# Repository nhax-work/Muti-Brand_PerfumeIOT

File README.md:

# Chạy dự án ở máy local — Hướng dẫn cho người mới

Tài liệu này giải thích **cách dựng database (và các dịch vụ đi kèm) trên máy của bạn** bằng Docker Compose, theo cách dễ hiểu nhất có thể. Đọc xong là chạy được, không cần biết Docker trước.

---

## 1. Docker Compose là gì, hiểu đơn giản

Coi `docker-compose.yml` như một **công thức nấu ăn**: nó ghi "cần 1 nồi Postgres, 1 nồi Redis, 1 nồi MQTT...". Khi bạn gõ lệnh `docker compose up`, máy bạn sẽ tự tải và bật các "nồi" đó lên — **trên chính máy bạn**, không đụng vào máy ai khác.

Điều quan trọng cần nhớ:

> **Database bằng Docker Compose là của riêng từng người.** Máy bạn có một DB, máy đồng đội có một DB khác. Hai DB này *không tự động giống nhau* — ban đầu cả hai đều **trống trơn**, không có bảng nào cả.

Vậy làm sao để DB của mọi người giống nhau? Câu trả lời ở mục 4.

---

## 2. Chuẩn bị lần đầu (chỉ làm 1 lần)

**Bước 1 — Cài Docker Desktop** (nếu chưa có): tải tại docker.com, cài xong nhớ mở app Docker Desktop lên và để nó chạy nền.

**Bước 2 — Tạo file cấu hình riêng của bạn:**

```bash
cp .env.example .env
```

File `.env` chứa các thông tin như tên user DB, mật khẩu, cổng kết nối... File này **không được commit lên git** (đã có trong `.gitignore` rồi, nên bạn không cần lo). Mỗi người tự có file `.env` riêng, thường copy y nguyên từ `.env.example` là chạy được, không cần sửa gì.

---

## 3. Bật hạ tầng lên

Từ thư mục gốc của repo, chạy:

```bash
make up
```

(Lệnh này thực chất chỉ là `docker compose up -d` — `make` là cách gõ tắt cho gọn.)

Lần đầu sẽ hơi lâu vì máy phải tải các "nồi" (image) về. Sau khi xong, kiểm tra mọi thứ đã bật chưa:

```bash
docker compose ps
```

Bạn sẽ thấy 5 dịch vụ:

| Dịch vụ | Là gì | Cổng mặc định |
|---|---|---|
| `db` | Database chính, dùng khi code | `localhost:5432` |
| `db-test` | Database riêng chỉ dùng khi chạy test tự động | `localhost:5433` |
| `redis` | Bộ nhớ đệm / hàng đợi | `localhost:6379` |
| `mqtt` | Máy chủ nhận tin nhắn từ thiết bị IoT | `localhost:1883` |
| `adminer` | Trang web xem DB bằng giao diện, đỡ phải gõ SQL | `localhost:8080` |

Muốn xem DB đang có gì bằng giao diện web, mở trình duyệt vào `http://localhost:8080`, đăng nhập bằng thông tin trong file `.env` (server = `db`, user/password/database lấy từ `.env`).

**Tắt hạ tầng khi không dùng nữa:**

```bash
make down
```

Dữ liệu vẫn được giữ lại (không mất), lần sau `make up` lại là có tiếp.

---

## 4. Vì sao cần "một người code trước" — và các bạn khác làm gì sau đó

Đây là phần quan trọng nhất, trả lời đúng câu hỏi bạn đang thắc mắc.

Khi mới `make up`, DB của bạn **trống hoàn toàn** — chưa có bảng `user`, `order`, `slot`... gì cả. Ai `up` lên cũng ra một DB trống giống hệt nhau về *cấu trúc rỗng*, nhưng chưa có *cấu trúc bảng (schema)* bên trong.

Vậy quy trình đúng là:

1. **Một bạn (TV1, theo phân công trong `spec/contracts/README.md`) là người viết schema đầu tiên.** Bạn ấy thiết kế bảng, cột, ràng buộc... trong file `spec/contracts/schema.sql`, dựa theo mô hình dữ liệu đã thống nhất ở `spec/glossary.md` và `spec/contracts/erd.md`.
2. Bạn ấy **không gõ tay vào DB của mình rồi thôi** — mà biến thiết kế đó thành **migration**: một tập lệnh có thể chạy lại được để "dựng" đúng các bảng đó lên bất kỳ DB trống nào.
3. Migration này được **commit vào git**. Đây là phần quan trọng: cái mọi người chia sẻ với nhau là **file migration**, chứ không phải database thật.
4. Từ lúc đó, mỗi bạn khác chỉ cần:

```bash
git pull          # lấy migration mới nhất
make up           # dựng DB trống (nếu chưa có)
make migrate      # cho migration "chạy" lên DB của mình -> tự sinh đúng các bảng
make seed         # (tuỳ chọn) nạp thêm dữ liệu mẫu để test cho dễ
```

Sau bước này, DB của bạn sẽ có **cấu trúc bảng giống hệt** DB của TV1 và mọi người khác — dù dữ liệu bên trong (do mỗi người tự thêm khi code/test) có thể khác nhau, điều đó không sao vì đó chỉ là dữ liệu thử.

> Ví dụ dễ hình dung: file migration giống như **bản vẽ thiết kế tủ**. Ai cũng tự đóng tủ ở nhà mình (tự tạo DB riêng), nhưng vì dùng chung một bản vẽ nên tủ ai cũng giống nhau về hình dạng, ngăn kéo. Đồ đựng bên trong tủ (dữ liệu) thì mỗi người khác nhau, không quan trọng.

**Mỗi khi có ai thêm/sửa bảng về sau:** người đó viết migration mới → commit. Người khác `git pull` xong nhớ chạy lại `make migrate` để đồng bộ. **Tuyệt đối không tự ý sửa tay cấu trúc DB của mình** rồi mong người khác tự giống — làm vậy sẽ sớm bị lệch, dẫn đến lỗi khó hiểu ("chạy ở máy tôi thì được mà").

### Chuẩn bị thêm cho lần đầu

`make migrate` và `make seed` đã chạy được thật (công cụ: **node-pg-migrate**, migration viết bằng
SQL thuần — chi tiết ở [docs/MIGRATIONS.md](docs/MIGRATIONS.md)). Trước lần chạy đầu tiên, làm thêm
hai việc:

**1. Cài thư viện Node** (chỉ một lần, và mỗi khi `package.json` đổi):

```bash
npm install
```

**2. Bổ sung hai dòng vào file `.env` của bạn** — `.env.example` đã có sẵn, nhưng nếu bạn tạo `.env`
từ trước thì nó còn thiếu:

```
DATABASE_URL=postgresql://scent:scent_dev@localhost:5432/scentstation
SEED_DEFAULT_PASSWORD=doi_gia_tri_nay
```

`DATABASE_URL` phải khớp với `DB_USER`, `DB_PASSWORD`, `DB_NAME`, `DB_PORT` trong cùng file.
`SEED_DEFAULT_PASSWORD` là mật khẩu cho các tài khoản mẫu — script seed **không chạy** nếu thiếu
biến này, vì không được hardcode mật khẩu trong mã nguồn.

---

## 5. Các lệnh hay dùng

| Lệnh | Tác dụng |
|---|---|
| `make up` | Bật db, redis, mqtt, adminer |
| `make down` | Tắt, nhưng **giữ lại** dữ liệu |
| `make logs` | Xem log của tất cả dịch vụ, để debug khi lỗi |
| `make reset` | **Xoá sạch** dữ liệu và dựng lại từ đầu — chỉ dùng khi DB của bạn bị lỗi lung tung, không cứu được |
| `make migrate` | Dựng cấu trúc bảng mới nhất lên DB của bạn |
| `make seed` | Nạp dữ liệu mẫu: 1 máy, 4 slot, 2 thương hiệu mỗi bên 2 slot |
| `make lint` | Kiểm tra style và kiểu dữ liệu |
| `make test` | Chạy toàn bộ test (trừ e2e) |

---

## 6. Lỗi hay gặp

**"Port đã được sử dụng" / port already in use:** máy bạn đang có chương trình khác dùng cổng đó (ví dụ Postgres cài sẵn dùng cổng 5432). Sửa bằng cách đổi số cổng trong file `.env` của riêng bạn, ví dụ `DB_PORT=5434`, rồi `make down` && `make up` lại.

**Docker Desktop chưa mở:** phải mở app Docker Desktop trước, để nó chạy nền, rồi mới chạy được `make up`.

**Muốn xoá hết làm lại từ đầu vì DB bị rối:** `make reset`. Lưu ý lệnh này xoá sạch dữ liệu trong DB của bạn (không ảnh hưởng người khác).

```bash
docker compose down -v
docker compose up -d
npm run db:migrate
npm run db:seed
```

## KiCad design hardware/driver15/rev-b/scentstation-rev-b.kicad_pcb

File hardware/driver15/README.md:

# Bo điều khiển 15 tải cho ScentStation

## Biến thể Rev B đồng 1 oz — 26/10/2026

Theo lựa chọn người dùng, đã tạo riêng [Gerber Rev B 1 oz](rev-b-1oz/ScentStation_RevB_1oz_Gerber_THU_NGHIEM.zip), [hồ sơ KiCad 1 oz](rev-b-1oz/ScentStation_RevB_1oz_HO_SO_DAY_DU.zip) và [hướng dẫn](rev-b-1oz/HUONG_DAN_REV_B_1OZ.md). Đồng 35 µm mỗi mặt, tổng dày bo 1,6 mm; giữ nguyên đường mạch/via. DRC mới: 0 vi phạm, 0 kết nối thiếu; đã đọc lại Gerber/khoan và đối chiếu lệnh hình học với bản 2 oz. Đây vẫn là mẫu thử cho chế độ một bơm + một van; chưa kiểm chứng dòng khởi động, nhiệt và mạ lỗ. Bản 2 oz bên dưới được giữ để tham chiếu.

## Rev B — khoảng cách socket ESP32 25 mm — 20/10/2026

Cập nhật theo phép đo người dùng: tâm hai hàng socket 25 mm, thay 27,5 mm của Rev A. Đã đi lại đường tín hiệu và kiểm tra DRC/ERC: 0 vi phạm, 0 kết nối thiếu; 381 chân khớp sơ đồ/PCB. Dùng [Gerber Rev B](rev-b/ScentStation_RevB_Gerber_THU_NGHIEM.zip), [hồ sơ KiCad Rev B](rev-b/ScentStation_RevB_HO_SO_DAY_DU.zip), [hướng dẫn](rev-b/HUONG_DAN_REV_B.md) và [mô hình GLB xem trên web](rev-b/3d/scentstation-web.glb). Đây vẫn là bản thử nghiệm; pinout ESP và linh kiện thực cần đối chiếu trước khi đặt in. Rev A bên dưới là bản cũ.

## Rev A đã đi dây và xuất Gerber — 19/10/2026

Xem [hướng dẫn Rev A](rev-a/HUONG_DAN_REV_A.md), [Gerber thử nghiệm](rev-a/ScentStation_RevA_Gerber_THU_NGHIEM.zip), [hồ sơ KiCad đầy đủ](rev-a/ScentStation_RevA_HO_SO_DAY_DU.zip) và [kết quả kiểm tra](rev-a/KIEM_TRA.json). Rev A là bo hai lớp 240 × 190 mm, đồng 70 µm mỗi mặt, giữ socket ESP tạm 27,5 mm. Không dùng các bản nháp phía dưới để đặt in. Rev A vẫn cần đối chiếu linh kiện/cơ khí và thử phần cứng trước khi duyệt sản xuất.

## Bản thiết kế không dùng load cell — 19/10/2026

Bổ sung [bố trí PCB nháp](pcb-nhap/README.md) theo yêu cầu người dùng: bo tạm 180 × 140 mm, socket ESP tạm 27,5 mm. Có file KiCad và ảnh bố trí; chưa có net điện hoặc đường đồng, không dùng đặt in.

Xem [thiết kế V1](THIET_KE_V1.md), [sơ đồ chức năng](so-do-v1.svg) và [bảng 15 kênh](kenh-v1.csv). Bản V1 giữ chân bơm/nút/đèn hiện tại, dùng PCF8575 + SN74AHCT04 cho van và bổ sung tín hiệu cho phép tải (đã cập nhật theo lựa chọn người dùng). Đây là tài liệu rà soát nguyên lý, chưa có PCB đi dây hoặc Gerber; các phần chưa chốt được ghi rõ trong tài liệu V1. Nội dung dưới đây là dữ liệu nền của bản dự thảo trước đó.

Trạng thái: thiết kế nguyên lý dự thảo ngày 15/10/2026, chưa đủ điều kiện xuất Gerber để sản xuất. Không thay đổi firmware đã thử ổn định; Report 3 đang tạm dừng theo yêu cầu.

## Dữ liệu đã xác nhận

| Hạng mục | Dữ liệu | Nguồn |
|---|---|---|
| Kiểu bo | MOSFET tích hợp, không dùng lại module MOSFET rời | Người dùng xác nhận |
| Tải | 5 bơm, 5 van, 5 đèn nút | Người dùng xác nhận |
| Bơm | DP-521, DC 12 V, dòng công bố 2 A, áp suất tối đa 0,48 MPa | Chữ trên ảnh sản phẩm người dùng gửi; chưa có datasheet nhà sản xuất |
| Nguồn | DC 12 V | Người dùng xác nhận; ảnh nguồn ghi S-120-12, cần đối chiếu nhãn thực tế để chốt dòng |
| Cầu chì | 5 A | Người dùng xác nhận; chưa biết loại nhanh/chậm, khả năng cắt và kích thước |
| Nút có đèn | Thân 16 mm; nhấn nhả, không giữ trạng thái; 5 chân: 2 LED và COM/NO/NC; LED 12–24 VDC | Ảnh thông số người dùng gửi; chưa có dòng LED |
| Van đã chọn | 2W025-08, DN08, ren G1/4, DC 12 V, 6 W; cút nối ống 8 mm; mô tả dòng sản phẩm là thường đóng | Ảnh thông số mới và lựa chọn mua người dùng gửi; dòng tính từ nhãn 6 W / 12 V = 0,5 A |
| ESP | ESP32 38 chân, ảnh module ESP32-WROOM-32D | Người dùng xác nhận và ảnh; khoảng cách hai hàng chân chưa đo |
| Diode đang có | 1N5819 Schottky, 1 A; datasheet Vishay: VRRM 40 V, DO-41 | Người dùng xác nhận mã; cần đối chiếu hãng linh kiện thực |
| Điện trở | Ảnh minh họa lặp lại | Không dùng ảnh để xác định giá trị điện trở thực mua |

## Ngân sách dòng điện

Một bơm theo dòng công bố: 12 V × 2 A = 24 W. Năm bơm cùng chạy: 10 A, 120 W, chưa tính van, đèn và mạch điều khiển. Cầu chì tổng 5 A không phục vụ chế độ đó. Nhãn 2 A cũng chưa xác định được dòng khởi động, dòng kẹt rotor hoặc dòng khi đầu bơm bị chặn.

Chế độ dự kiến là một cụm bơm + van hoạt động tại một thời điểm. Dòng qua cầu chì khi đó là dòng bơm thực tế + dòng van đang mở + tổng dòng đèn đang sáng + dòng vào bộ hạ áp. Phải đo cả xung khởi động trước khi chốt nguồn, cầu chì, đầu nối và đường đồng. Không tăng cầu chì đơn thuần để khắc phục sụt nguồn. Mạch phải chịu và bảo vệ được lỗi nhiều kênh cùng bật, không dựa riêng vào giới hạn một bơm trong firmware.

Ảnh van bổ sung xác nhận công suất 6 W tại DC 12 V: dòng danh định tính toán 0,5 A/van. Một bơm 2 A và một van 0,5 A tương ứng khoảng 2,5 A, 30 W, chưa tính đèn, nguồn logic và xung khởi động bơm. Năm cặp bơm/van cùng chạy tương ứng 12,5 A, 150 W trước các tải phụ; không phù hợp cầu chì tổng 5 A. Đây là tính toán từ thông số công bố, chưa phải phép đo tải. Van có thể duy trì mở lâu hơn bơm nên cần xét nhiệt liên tục của kênh van, không lấy chu kỳ bơm 500 ms làm chu kỳ van.

## Kiến trúc nguyên lý đề xuất

**Đã giải quyết khác biệt điện áp:** ảnh lựa chọn xác nhận DC 12 V và ống 8 mm; ảnh thông số bổ sung ghi 2W025-08, 6 W. Đoạn mô tả 220 V trước đó thuộc bài bán nhiều biến thể, không dùng làm điện áp cho van đã chọn. Tiếp tục kiến trúc bo tải 12 VDC. Vẫn cần kiểm tra phân cực hoặc diode có sẵn, yêu cầu thời gian nhả và nhãn sản phẩm thực để chốt bảo vệ. Ren G1/4/DN08 là thông số thân van; ống 8 mm là cút lắp ngoài, không phải bề rộng lỗ PCB.

12 V đi qua bảo vệ/cầu chì đến bus tải. Mỗi tải có đầu nối riêng: cực dương về bus 12 V được bảo vệ; cực âm về Drain MOSFET N; Source về mass công suất. Mass logic và mass công suất có tham chiếu chung nhưng đường hồi bơm không chạy qua ESP. Mỗi bơm và van có mạch dập xung đặt gần vòng dòng chuyển mạch; loại diode/clamp cần kiểm tra dòng, năng lượng và thời gian nhả van.

Diode 1N5819 đang có được đề xuất cho từng cuộn van 12 V, dòng danh định tính toán 0,5 A, với điều kiện kiểm tra nhiệt, xung lặp và thời gian nhả. Khi dùng diode flyback song song tải DC: cathode đầu có vạch về +12 V, anode về đầu âm tải/Drain; diode bị phân cực ngược khi tải được cấp điện. Diode thông thường có thể kéo dài thời gian nhả van, cần kiểm tra ảnh hưởng đến liều. Không chốt 1N5819 cho bơm 2 A chỉ dựa vào định mức xung đơn: cần diode có đường đặc tính dòng xung lặp/nhiệt đáp ứng dòng tại lúc ngắt và dòng khởi động/kẹt thực tế. Không dùng 1N5819 nối tiếp bus tổng 5 A và không mặc định mắc song song nhiều diode để tăng dòng.

Đề xuất dùng AOD4184A TO-252/DPAK với tầng đệm SN74AHCT541 cấp 5 V. AOD4184A có RDS(on) tối đa 9,5 mΩ tại VGS=4,5 V; datasheet không đảm bảo thông số đó ở 3,3 V. Vì vậy không lấy điện áp ngưỡng VGS(th) làm bằng chứng MOSFET mở đủ khi nối trực tiếp GPIO. Với 2 A và 9,5 mΩ, tổn hao dẫn tham khảo ở điều kiện datasheet là 0,038 W, chưa tính tăng nhiệt, chuyển mạch và dòng khởi động. Không dùng dòng 50 A trên datasheet làm định mức của PCB.

Hai SN74AHCT541 cung cấp tối đa 16 đường đệm; ngõ OE giữ trạng thái vô hiệu bằng điện trở khi khởi động, ngõ Gate mỗi MOSFET có điện trở kéo xuống riêng. Đường enable của ESP cần tầng kéo xuống/chuyển mức thích hợp để không đưa 5 V vào GPIO. Giá trị điện trở Gate, mạng bảo vệ và trình tự cấp nguồn chưa chốt trước kiểm tra thời gian chuyển mạch.

Giữ 10 GPIO bơm/đèn đã test. Đề xuất thêm MCP23017 cấp 3,3 V qua I2C GPIO16/17 cho 5 van; tín hiệu van cũng qua tầng đệm. Đây là phương án cần kiểm tra nguồn chính thức của linh kiện và triển khai firmware riêng, chưa phải chân van hiện có trong code. Đường enable phần cứng phải tắt được tải kể cả khi bus I2C treo. ESP38 chân không còn nghĩa mọi GPIO đều dùng được: tránh chân flash, chân chỉ-input và các chân strap trong phương án bố trí mới.

Nguồn logic cần bộ hạ áp 12 V → 5 V được chọn và kiểm tra riêng, không cấp 12 V trực tiếp vào ESP. Chưa chốt bộ hạ áp tích hợp hay module; cần tránh cấp ngược giữa USB và nguồn 5 V ngoài. Chưa tạo footprint ESP từ ảnh vì chưa đo khoảng cách hàng chân và vị trí USB/antenna.

## Chân đang giữ lại từ bản máy đã test

| Cụm | Bơm | Đèn | Nút NO |
|---|---|---|---|
| 1 | GPIO25 | GPIO26 | GPIO27 |
| 2 | GPIO18 | GPIO23 | GPIO34 |
| 3 | GPIO19 | GPIO32 | GPIO35 |
| 4 | GPIO21 | GPIO33 | GPIO36 |
| 5 | GPIO22 | GPIO13 | GPIO39 |

Nút COM về GND; mỗi nút kéo lên 3V3 bằng 10 kΩ, đặc biệt GPIO34/35/36/39 không có pull-up nội. Không đưa nguồn đèn 12 V vào chân tiếp điểm hoặc GPIO.

Theo ảnh thông số mới, LED dùng 12–24 VDC nên nhánh đèn của bo có thể dùng nguồn 12 V. Dòng 3 A tại 36 V là định mức tiếp điểm, không phải dòng LED; không lấy 3 A để tính công suất mỗi đèn. Đèn LED+ nối bus 12 V được bảo vệ, LED− nối Drain kênh MOSFET đèn; cực Source về GND công suất. Phần tiếp điểm riêng: COM về GND tín hiệu, NO về GPIO nút, NC để trống. Cần xác định chính xác chân LED+/LED− trên mẫu thực tế trước khi đấu; mô tả 5 chân chưa cho biết vị trí vật lý. Không tự bỏ hoặc thêm điện trở hạn dòng dựa trên hình: cần xác nhận cấu tạo nhánh LED 12–24 V và dòng tại 12 V. Kích thước thân 16 mm không thay thế bản vẽ lỗ lắp/cốt ren để gia công mica.

## Dữ liệu còn cần để chốt

1. Phân cực/diode sẵn, yêu cầu thời gian nhả và xác nhận nhãn van thực tế. Model 2W025-08, DC 12 V, 6 W, dòng tính 0,5 A và cút ống 8 mm đã có trong ảnh thông số; không cần hỏi lại công suất danh định.
2. Dòng LED tại 12 V và vị trí chân LED+/LED− trên mẫu thật; điện áp LED đã xác nhận 12–24 VDC, tiếp điểm COM/NO/NC tách riêng.
3. Dòng định mức nguồn trên nhãn thực tế và đo dòng khởi động từng bơm dưới tải thực.
4. Chế độ van: mở trước bơm bao lâu, đóng sau bao lâu; chỉ một van mở hay nhiều van cùng mở.
5. Kích thước bo, vị trí lỗ bắt, loại đầu nối và tiết diện dây; khoảng cách hai hàng chân ESP đo bằng thước/cặp.

## Điều kiện trước khi gửi đặt in

Chốt sơ đồ và BOM theo dữ liệu trên; kiểm ERC; layout theo dòng và nhiệt thực; kiểm DRC và kết nối ngược từ layout; kiểm kích thước footprint/đầu nối; xuất đủ đồng, solder mask, silkscreen, outline và drill; mở lại bộ Gerber/drill trong viewer; chốt báo giá, số lượng và địa chỉ nhận. Hiện chưa có file Gerber, chưa đặt hàng hoặc phát sinh chi phí.

Nguồn linh kiện đã tra: [AOD4184A datasheet AOS](https://www.aosmd.com/res/data_sheets/AOD4184A.pdf), [SN74AHCT541 datasheet TI](https://www.ti.com/lit/ds/symlink/sn74ahct541.pdf). Thông số bơm và nguồn từ ảnh bán hàng cần xác nhận trên phần cứng thực.

Nguồn diode: [1N5819 Vishay datasheet](https://www.vishay.com/docs/88525/1n5817.pdf). Định mức 1 A là dòng chỉnh lưu trung bình theo điều kiện datasheet, không phải bảo đảm cho mọi xung dập tải cảm.

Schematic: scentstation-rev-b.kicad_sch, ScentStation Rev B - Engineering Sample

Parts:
C5: 470u_10V; CP_Radial_D8.0mm_P3.50mm
C12: 1000u_35V; CP_Radial_D12.5mm_P5.00mm
CB1, CB2: 1u; C_0805_2012Metric
CBTN1, CBTN2, CBTN3, CBTN4, CBTN5: 100n; C_0805_2012Metric
CPCF1: 100n; C_0805_2012Metric
CU1, CU2, CU5, CU6: 100n; C_0805_2012Metric
CWD1: 1u_X7R; C_0805_2012Metric
D1, D2, D3, D4, D5, D6, D7, D8, D9, D10: SB560_5A_60V; D_DO-201AD_P12.70mm_Horizontal
DTVS1: SMBJ15A; D_SMB
J5: FROM_BUCK_5V; PhoenixContact_MSTBVA_2,5_2-G-5,08_1x02_P5.08mm_Vertical
J12: 12V_INPUT_EXTERNAL_FUSE_5A_REQUIRED; PhoenixContact_MSTBVA_2,5_2-G-5,08_1x02_P5.08mm_Vertical
JBTN1, JBTN2, JBTN3, JBTN4, JBTN5: BUTTON_COM_NO; PinHeader_1x02_P2.54mm_Vertical
JBUCKIN1: TO_BUCK_INPUT; PhoenixContact_MSTBVA_2,5_2-G-5,08_1x02_P5.08mm_Vertical
JESPL1: ESP32_1x19_SPACING_25_MEASURED; PinSocket_1x19_P2.54mm_Vertical
JESPR1: ESP32_1x19_SPACING_25_MEASURED; PinSocket_1x19_P2.54mm_Vertical
JLIGHT1: LIGHT1_PLUS_MINUS; PhoenixContact_MSTBVA_2,5_2-G-5,08_1x02_P5.08mm_Vertical
JLIGHT2: LIGHT2_PLUS_MINUS; PhoenixContact_MSTBVA_2,5_2-G-5,08_1x02_P5.08mm_Vertical
JLIGHT3: LIGHT3_PLUS_MINUS; PhoenixContact_MSTBVA_2,5_2-G-5,08_1x02_P5.08mm_Vertical
JLIGHT4: LIGHT4_PLUS_MINUS; PhoenixContact_MSTBVA_2,5_2-G-5,08_1x02_P5.08mm_Vertical
JLIGHT5: LIGHT5_PLUS_MINUS; PhoenixContact_MSTBVA_2,5_2-G-5,08_1x02_P5.08mm_Vertical
JP5: REMOVE_FOR_USB; PinHeader_1x02_P2.54mm_Vertical
JPCF1: PCF8575_EXTERNAL_3V3; PinHeader_1x10_P2.54mm_Vertical
JPUMP1: PUMP1_PLUS_MINUS; PhoenixContact_MSTBVA_2,5_2-G-5,08_1x02_P5.08mm_Vertical
JPUMP2: PUMP2_PLUS_MINUS; PhoenixContact_MSTBVA_2,5_2-G-5,08_1x02_P5.08mm_Vertical
JPUMP3: PUMP3_PLUS_MINUS; PhoenixContact_MSTBVA_2,5_2-G-5,08_1x02_P5.08mm_Vertical
JPUMP4: PUMP4_PLUS_MINUS; PhoenixContact_MSTBVA_2,5_2-G-5,08_1x02_P5.08mm_Vertical
JPUMP5: PUMP5_PLUS_MINUS; PhoenixContact_MSTBVA_2,5_2-G-5,08_1x02_P5.08mm_Vertical
JSTOP1: INTERLOCK_NC_REQUIRED; PinHeader_1x02_P2.54mm_Vertical
JVALVE1: VALVE1_PLUS_MINUS; PhoenixContact_MSTBVA_2,5_2-G-5,08_1x02_P5.08mm_Vertical
JVALVE2: VALVE2_PLUS_MINUS; PhoenixContact_MSTBVA_2,5_2-G-5,08_1x02_P5.08mm_Vertical
JVALVE3: VALVE3_PLUS_MINUS; PhoenixContact_MSTBVA_2,5_2-G-5,08_1x02_P5.08mm_Vertical
JVALVE4: VALVE4_PLUS_MINUS; PhoenixContact_MSTBVA_2,5_2-G-5,08_1x02_P5.08mm_Vertical
JVALVE5: VALVE5_PLUS_MINUS; PhoenixContact_MSTBVA_2,5_2-G-5,08_1x02_P5.08mm_Vertical
Q1, Q2, Q3, Q4, Q5, Q6, Q7, Q8, Q9, Q10, Q11, Q12, Q13, Q14, Q15: AOD4184A; TO-252-2
QEN1, QEN2, QEN3: 2N3904; TO-92_Inline_Wide
RBTN1, RBTN2, RBTN3, RBTN4, RBTN5: 10k; R_0805_2012Metric
RENB1, RENB2, RENB3: 10k; R_0805_2012Metric
RENP1, RENP2, RENP3: 100k; R_0805_2012Metric
RG1, RG2, RG3, RG4, RG5, RG6, RG7, RG8, RG9, RG10, RG11, RG12, RG13, RG14, RG15: 1k; R_0805_2012Metric
RHB1: 10k; R_0805_2012Metric
RI2C1, RI2C2: 4.7k; R_0805_2012Metric
RIN11, RIN12, RIN13, RIN14, RIN15, RIN23, RIN24, RIN25, RIN26, RIN27: 47k; R_0805_2012Metric
ROE1: 10k; R_0805_2012Metric
RPCF0, RPCF1, RPCF2, RPCF3, RPCF4, RPCF5: 10k; R_0805_2012Metric
RPD1, RPD2, RPD3, RPD4, RPD5, RPD6, RPD7, RPD8, RPD9, RPD10, RPD11, RPD12, RPD13, RPD14, RPD15: 100k; R_0805_2012Metric
RRUN1: 10k; R_0805_2012Metric
RWD1: 470k_1pct; R_0805_2012Metric
U1, U2: SN74AHCT541N; DIP-20_W7.62mm
U5: SN74AHCT04N; DIP-14_W7.62mm
U6: CD74HC123E; DIP-16_W7.62mm

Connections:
3V3: CPCF1.1 (3V3), CU6.1 (3V3), JESPL1.1 (3V3), JPCF1.1 (3V3), RBTN1.1 (3V3), RBTN2.1 (3V3), RBTN3.1 (3V3), RBTN4.1 (3V3), RBTN5.1 (3V3), RI2C1.1 (3V3), RI2C2.1 (3V3), RPCF0.1 (3V3), RPCF1.1 (3V3), RPCF2.1 (3V3), RPCF3.1 (3V3), RPCF4.1 (3V3), RPCF5.1 (3V3), RWD1.1 (3V3), U6.16 (VCC)
5V: C5.1 (5V), CB1.1 (5V), CB2.1 (5V), CU1.1 (5V), CU2.1 (5V), CU5.1 (5V), JESPL1.19 (5V), JP5.2 (5V), ROE1.1 (5V), U1.20 (VCC), U2.20 (VCC), U5.14 (VCC)
5V_EXT: J5.1 (5V_EXT), JP5.1 (5V_EXT)
12V_LOAD: C12.1 (12V_LOAD), D1.1 (K), D2.1 (K), D3.1 (K), D4.1 (K), D5.1 (K), D6.1 (K), D7.1 (K), D8.1 (K), D9.1 (K), D10.1 (K), DTVS1.1 (K), J12.1 (12V_LOAD), JBUCKIN1.1 (12V_LOAD), JLIGHT1.1 (12V_LOAD), JLIGHT2.1 (12V_LOAD), JLIGHT3.1 (12V_LOAD), JLIGHT4.1 (12V_LOAD), JLIGHT5.1 (12V_LOAD), JPUMP1.1 (12V_LOAD), JPUMP2.1 (12V_LOAD), JPUMP3.1 (12V_LOAD), JPUMP4.1 (12V_LOAD), JPUMP5.1 (12V_LOAD), JVALVE1.1 (12V_LOAD), JVALVE2.1 (12V_LOAD), JVALVE3.1 (12V_LOAD), JVALVE4.1 (12V_LOAD), JVALVE5.1 (12V_LOAD)
BUF1_1: RG1.1 (BUF1_1), U1.18 (Y1)
BUF1_2: RG2.1 (BUF1_2), U1.17 (Y2)
BUF1_3: RG3.1 (BUF1_3), U1.16 (Y3)
BUF1_4: RG4.1 (BUF1_4), U1.15 (Y4)
BUF1_5: RG5.1 (BUF1_5), U1.14 (Y5)
BUF1_6: RG6.1 (BUF1_6), U1.13 (Y6)
BUF1_7: RG7.1 (BUF1_7), U1.12 (Y7)
BUF1_8: RG8.1 (BUF1_8), U1.11 (Y8)
BUF2_1: RG9.1 (BUF2_1), U2.18 (Y1)
BUF2_2: RG10.1 (BUF2_2), U2.17 (Y2)
BUF2_3: RG11.1 (BUF2_3), U2.16 (Y3)
BUF2_4: RG12.1 (BUF2_4), U2.15 (Y4)
BUF2_5: RG13.1 (BUF2_5), U2.14 (Y5)
BUF2_6: RG14.1 (BUF2_6), U2.13 (Y6)
BUF2_7: RG15.1 (BUF2_7), U2.12 (Y7)
DRAIN1: D1.2 (A), JPUMP1.2 (DRAIN1), Q1.2 (D)
DRAIN2: D2.2 (A), JPUMP2.2 (DRAIN2), Q2.2 (D)
DRAIN3: D3.2 (A), JPUMP3.2 (DRAIN3), Q3.2 (D)
DRAIN4: D4.2 (A), JPUMP4.2 (DRAIN4), Q4.2 (D)
DRAIN5: D5.2 (A), JPUMP5.2 (DRAIN5), Q5.2 (D)
DRAIN6: D6.2 (A), JVALVE1.2 (DRAIN6), Q6.2 (D)
DRAIN7: D7.2 (A), JVALVE2.2 (DRAIN7), Q7.2 (D)
DRAIN8: D8.2 (A), JVALVE3.2 (DRAIN8), Q8.2 (D)
DRAIN9: D9.2 (A), JVALVE4.2 (DRAIN9), Q9.2 (D)
DRAIN10: D10.2 (A), JVALVE5.2 (DRAIN10), Q10.2 (D)
DRAIN11: JLIGHT1.2 (DRAIN11), Q11.2 (D)
DRAIN12: JLIGHT2.2 (DRAIN12), Q12.2 (D)
DRAIN13: JLIGHT3.2 (DRAIN13), Q13.2 (D)
DRAIN14: JLIGHT4.2 (DRAIN14), Q14.2 (D)
DRAIN15: JLIGHT5.2 (DRAIN15), Q15.2 (D)
EN_B1: QEN1.2 (B), RENB1.2 (EN_B1), RENP1.1 (EN_B1)
EN_B2: QEN2.2 (B), RENB2.2 (EN_B2), RENP2.1 (EN_B2)
EN_B3: QEN3.2 (B), RENB3.2 (EN_B3), RENP3.1 (EN_B3)
EN_CHAIN1: QEN1.1 (E), QEN2.3 (C)
EN_CHAIN2: QEN2.1 (E), QEN3.3 (C)
ESP_EN: JESPL1.2 (ESP_EN), U6.3 (/1CLR)
EXP_READY: RENB2.1 (EXP_READY), U5.12 (6Y)
GATE1: Q1.1 (G), RG1.2 (GATE1), RPD1.1 (GATE1)
GATE2: Q2.1 (G), RG2.2 (GATE2), RPD2.1 (GATE2)
GATE3: Q3.1 (G), RG3.2 (GATE3), RPD3.1 (GATE3)
GATE4: Q4.1 (G), RG4.2 (GATE4), RPD4.1 (GATE4)
GATE5: Q5.1 (G), RG5.2 (GATE5), RPD5.1 (GATE5)
GATE6: Q6.1 (G), RG6.2 (GATE6), RPD6.1 (GATE6)
GATE7: Q7.1 (G), RG7.2 (GATE7), RPD7.1 (GATE7)
GATE8: Q8.1 (G), RG8.2 (GATE8), RPD8.1 (GATE8)
GATE9: Q9.1 (G), RG9.2 (GATE9), RPD9.1 (GATE9)
GATE10: Q10.1 (G), RG10.2 (GATE10), RPD10.1 (GATE10)
GATE11: Q11.1 (G), RG11.2 (GATE11), RPD11.1 (GATE11)
GATE12: Q12.1 (G), RG12.2 (GATE12), RPD12.1 (GATE12)
GATE13: Q13.1 (G), RG13.2 (GATE13), RPD13.1 (GATE13)
GATE14: Q14.1 (G), RG14.2 (GATE14), RPD14.1 (GATE14)
GATE15: Q15.1 (G), RG15.2 (GATE15), RPD15.1 (GATE15)
GND: C5.2 (GND), C12.2 (GND), CB1.2 (GND), CB2.2 (GND), CBTN1.2 (GND), CBTN2.2 (GND), CBTN3.2 (GND), CBTN4.2 (GND), CBTN5.2 (GND), CPCF1.2 (GND), CU1.2 (GND), CU2.2 (GND), CU5.2 (GND), CU6.2 (GND), DTVS1.2 (A), J5.2 (GND), J12.2 (GND), JBTN1.1 (GND), JBTN2.1 (GND), JBTN3.1 (GND), JBTN4.1 (GND), JBTN5.1 (GND), JBUCKIN1.2 (GND), JESPL1.14 (GND), JESPR1.1 (GND), JESPR1.7 (GND), JPCF1.2 (GND), Q1.3 (S), Q2.3 (S), Q3.3 (S), Q4.3 (S), Q5.3 (S), Q6.3 (S), Q7.3 (S), Q8.3 (S), Q9.3 (S), Q10.3 (S), Q11.3 (S), Q12.3 (S), Q13.3 (S), Q14.3 (S), Q15.3 (S), QEN3.1 (E), RENP1.2 (GND), RENP2.2 (GND), RENP3.2 (GND), RHB1.2 (GND), RIN11.2 (GND), RIN12.2 (GND), RIN13.2 (GND), RIN14.2 (GND), RIN15.2 (GND), RIN23.2 (GND), RIN24.2 (GND), RIN25.2 (GND), RIN26.2 (GND), RIN27.2 (GND), RPD1.2 (GND), RPD2.2 (GND), RPD3.2 (GND), RPD4.2 (GND), RPD5.2 (GND), RPD6.2 (GND), RPD7.2 (GND), RPD8.2 (GND), RPD9.2 (GND), RPD10.2 (GND), RPD11.2 (GND), RPD12.2 (GND), RPD13.2 (GND), RPD14.2 (GND), RPD15.2 (GND), RRUN1.2 (GND), U1.10 (GND), U2.9 (A8), U2.10 (GND), U5.7 (GND), U6.1 (/1A), U6.8 (GND), U6.9 (/2A), U6.10 (2B), U6.11 (/2CLR)
GPIO4: JESPR1.13 (GPIO4), RHB1.1 (GPIO4), U6.2 (1B)
GPIO13: JESPL1.15 (GPIO13), RIN27.1 (GPIO13), U2.8 (A7)
GPIO14: JESPL1.12 (GPIO14), RENB1.1 (GPIO14), RRUN1.1 (GPIO14)
GPIO16: JESPR1.12 (GPIO16), JPCF1.3 (GPIO16), RI2C1.2 (GPIO16)
GPIO17: JESPR1.11 (GPIO17), JPCF1.4 (GPIO17), RI2C2.2 (GPIO17)
GPIO18: JESPR1.9 (GPIO18), RIN12.1 (GPIO18), U1.3 (A2)
GPIO19: JESPR1.8 (GPIO19), RIN13.1 (GPIO19), U1.4 (A3)
GPIO21: JESPR1.6 (GPIO21), RIN14.1 (GPIO21), U1.5 (A4)
GPIO22: JESPR1.3 (GPIO22), RIN15.1 (GPIO22), U1.6 (A5)
GPIO23: JESPR1.2 (GPIO23), RIN24.1 (GPIO23), U2.5 (A4)
GPIO25: JESPL1.9 (GPIO25), RIN11.1 (GPIO25), U1.2 (A1)
GPIO26: JESPL1.10 (GPIO26), RIN23.1 (GPIO26), U2.4 (A3)
GPIO27: CBTN1.1 (GPIO27), JBTN1.2 (GPIO27), JESPL1.11 (GPIO27), RBTN1.2 (GPIO27)
GPIO32: JESPL1.7 (GPIO32), RIN25.1 (GPIO32), U2.6 (A5)
GPIO33: JESPL1.8 (GPIO33), RIN26.1 (GPIO33), U2.7 (A6)
GPIO34: CBTN2.1 (GPIO34), JBTN2.2 (GPIO34), JESPL1.5 (GPIO34), RBTN2.2 (GPIO34)
GPIO35: CBTN3.1 (GPIO35), JBTN3.2 (GPIO35), JESPL1.6 (GPIO35), RBTN3.2 (GPIO35)
GPIO36: CBTN4.1 (GPIO36), JBTN4.2 (GPIO36), JESPL1.3 (GPIO36), RBTN4.2 (GPIO36)
GPIO39: CBTN5.1 (GPIO39), JBTN5.2 (GPIO39), JESPL1.4 (GPIO39), RBTN5.2 (GPIO39)
OE_N: QEN1.3 (C), ROE1.2 (OE_N), U1.1 (/OE1), U1.19 (/OE2), U2.1 (/OE1), U2.19 (/OE2)
PCF_P00: JPCF1.5 (PCF_P00), RPCF0.2 (PCF_P00), U5.1 (1A)
PCF_P01: JPCF1.6 (PCF_P01), RPCF1.2 (PCF_P01), U5.3 (2A)
PCF_P02: JPCF1.7 (PCF_P02), RPCF2.2 (PCF_P02), U5.5 (3A)
PCF_P03: JPCF1.8 (PCF_P03), RPCF3.2 (PCF_P03), U5.9 (4A)
PCF_P04: JPCF1.9 (PCF_P04), RPCF4.2 (PCF_P04), U5.11 (5A)
PCF_P05: JPCF1.10 (PCF_P05), RPCF5.2 (PCF_P05), U5.13 (6A)
VALVE1: U1.7 (A6), U5.2 (1Y)
VALVE2: U1.8 (A7), U5.4 (2Y)
VALVE3: U1.9 (A8), U5.6 (3Y)
VALVE4: U2.2 (A1), U5.8 (4Y)
VALVE5: U2.3 (A2), U5.10 (5Y)
WD_CNEG: CWD1.2 (WD_CNEG), U6.14 (1CEXT)
WD_LINK: JSTOP1.2 (WD_LINK), RENB3.1 (WD_LINK)
WD_OK: JSTOP1.1 (WD_OK), U6.13 (1Q)
WD_RC: CWD1.1 (WD_RC), RWD1.2 (WD_RC), U6.15 (1REXT_CEXT)

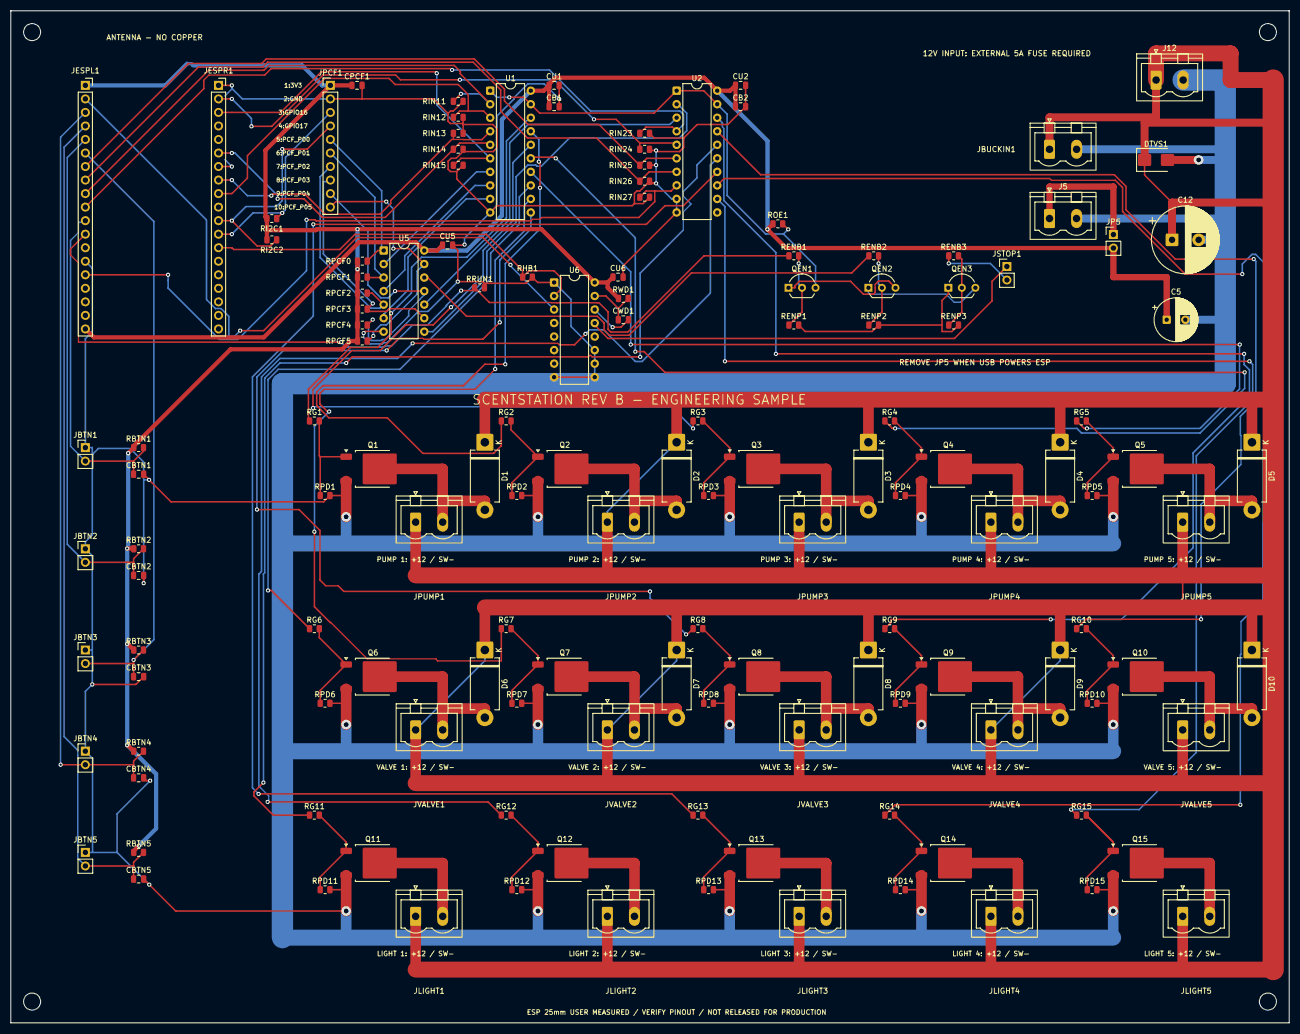
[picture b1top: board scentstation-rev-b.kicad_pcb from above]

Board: 2 copper layers, 240.0 x 190.0 mm, 143 parts (0 on the bottom side), 92 nets.

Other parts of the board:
H1, H2, H3, H4: M3; MountingHole_3.2mm_M3

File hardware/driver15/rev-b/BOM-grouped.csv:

Value,Footprint,Quantity,References
1000u_35V,Capacitor_THT:CP_Radial_D12.5mm_P5.00mm,1,C12
100k,Resistor_SMD:R_0805_2012Metric,18,RENP1 RENP2 RENP3 RPD1 RPD2 RPD3 RPD4 RPD5 RPD6 RPD7 RPD8 RPD9 RPD10 RPD11 RPD12 RPD13 RPD14 RPD15
100n,Capacitor_SMD:C_0805_2012Metric,10,CPCF1 CU5 CU1 CU2 CU6 CBTN1 CBTN2 CBTN3 CBTN4 CBTN5
10k,Resistor_SMD:R_0805_2012Metric,17,RPCF0 RPCF1 RPCF2 RPCF3 RPCF4 RPCF5 RHB1 RRUN1 RENB1 RENB2 RENB3 ROE1 RBTN1 RBTN2 RBTN3 RBTN4 RBTN5
12V_INPUT_EXTERNAL_FUSE_5A_REQUIRED,"Connector_Phoenix_MSTB:PhoenixContact_MSTBVA_2,5_2-G-5,08_1x02_P5.08mm_Vertical",1,J12
1k,Resistor_SMD:R_0805_2012Metric,15,RG1 RG2 RG3 RG4 RG5 RG6 RG7 RG8 RG9 RG10 RG11 RG12 RG13 RG14 RG15
1u,Capacitor_SMD:C_0805_2012Metric,2,CB1 CB2
1u_X7R,Capacitor_SMD:C_0805_2012Metric,1,CWD1
2N3904,Package_TO_SOT_THT:TO-92_Inline_Wide,3,QEN1 QEN2 QEN3
4.7k,Resistor_SMD:R_0805_2012Metric,2,RI2C1 RI2C2
470k_1pct,Resistor_SMD:R_0805_2012Metric,1,RWD1
470u_10V,Capacitor_THT:CP_Radial_D8.0mm_P3.50mm,1,C5
47k,Resistor_SMD:R_0805_2012Metric,10,RIN11 RIN12 RIN13 RIN14 RIN15 RIN23 RIN24 RIN25 RIN26 RIN27
AOD4184A,Package_TO_SOT_SMD:TO-252-2,15,Q1 Q2 Q3 Q4 Q5 Q6 Q7 Q8 Q9 Q10 Q11 Q12 Q13 Q14 Q15
BUTTON_COM_NO,Connector_PinHeader_2.54mm:PinHeader_1x02_P2.54mm_Vertical,5,JBTN1 JBTN2 JBTN3 JBTN4 JBTN5
CD74HC123E,Package_DIP:DIP-16_W7.62mm,1,U6
ESP32_1x19_SPACING_25_MEASURED,Connector_PinSocket_2.54mm:PinSocket_1x19_P2.54mm_Vertical,2,JESPL1 JESPR1
FROM_BUCK_5V,"Connector_Phoenix_MSTB:PhoenixContact_MSTBVA_2,5_2-G-5,08_1x02_P5.08mm_Vertical",1,J5
INTERLOCK_NC_REQUIRED,Connector_PinHeader_2.54mm:PinHeader_1x02_P2.54mm_Vertical,1,JSTOP1
LIGHT1_PLUS_MINUS,"Connector_Phoenix_MSTB:PhoenixContact_MSTBVA_2,5_2-G-5,08_1x02_P5.08mm_Vertical",1,JLIGHT1
LIGHT2_PLUS_MINUS,"Connector_Phoenix_MSTB:PhoenixContact_MSTBVA_2,5_2-G-5,08_1x02_P5.08mm_Vertical",1,JLIGHT2
LIGHT3_PLUS_MINUS,"Connector_Phoenix_MSTB:PhoenixContact_MSTBVA_2,5_2-G-5,08_1x02_P5.08mm_Vertical",1,JLIGHT3
LIGHT4_PLUS_MINUS,"Connector_Phoenix_MSTB:PhoenixContact_MSTBVA_2,5_2-G-5,08_1x02_P5.08mm_Vertical",1,JLIGHT4
LIGHT5_PLUS_MINUS,"Connector_Phoenix_MSTB:PhoenixContact_MSTBVA_2,5_2-G-5,08_1x02_P5.08mm_Vertical",1,JLIGHT5
M3,MountingHole:MountingHole_3.2mm_M3,4,H1 H2 H3 H4
PCF8575_EXTERNAL_3V3,Connector_PinHeader_2.54mm:PinHeader_1x10_P2.54mm_Vertical,1,JPCF1
PUMP1_PLUS_MINUS,"Connector_Phoenix_MSTB:PhoenixContact_MSTBVA_2,5_2-G-5,08_1x02_P5.08mm_Vertical",1,JPUMP1
PUMP2_PLUS_MINUS,"Connector_Phoenix_MSTB:PhoenixContact_MSTBVA_2,5_2-G-5,08_1x02_P5.08mm_Vertical",1,JPUMP2
PUMP3_PLUS_MINUS,"Connector_Phoenix_MSTB:PhoenixContact_MSTBVA_2,5_2-G-5,08_1x02_P5.08mm_Vertical",1,JPUMP3
PUMP4_PLUS_MINUS,"Connector_Phoenix_MSTB:PhoenixContact_MSTBVA_2,5_2-G-5,08_1x02_P5.08mm_Vertical",1,JPUMP4
PUMP5_PLUS_MINUS,"Connector_Phoenix_MSTB:PhoenixContact_MSTBVA_2,5_2-G-5,08_1x02_P5.08mm_Vertical",1,JPUMP5
REMOVE_FOR_USB,Connector_PinHeader_2.54mm:PinHeader_1x02_P2.54mm_Vertical,1,JP5
SB560_5A_60V,Diode_THT:D_DO-201AD_P12.70mm_Horizontal,10,D1 D2 D3 D4 D5 D6 D7 D8 D9 D10
SMBJ15A,Diode_SMD:D_SMB,1,DTVS1
SN74AHCT04N,Package_DIP:DIP-14_W7.62mm,1,U5
SN74AHCT541N,Package_DIP:DIP-20_W7.62mm,2,U1 U2
TO_BUCK_INPUT,"Connector_Phoenix_MSTB:PhoenixContact_MSTBVA_2,5_2-G-5,08_1x02_P5.08mm_Vertical",1,JBUCKIN1
VALVE1_PLUS_MINUS,"Connector_Phoenix_MSTB:PhoenixContact_MSTBVA_2,5_2-G-5,08_1x02_P5.08mm_Vertical",1,JVALVE1
VALVE2_PLUS_MINUS,"Connector_Phoenix_MSTB:PhoenixContact_MSTBVA_2,5_2-G-5,08_1x02_P5.08mm_Vertical",1,JVALVE2
VALVE3_PLUS_MINUS,"Connector_Phoenix_MSTB:PhoenixContact_MSTBVA_2,5_2-G-5,08_1x02_P5.08mm_Vertical",1,JVALVE3
VALVE4_PLUS_MINUS,"Connector_Phoenix_MSTB:PhoenixContact_MSTBVA_2,5_2-G-5,08_1x02_P5.08mm_Vertical",1,JVALVE4
VALVE5_PLUS_MINUS,"Connector_Phoenix_MSTB:PhoenixContact_MSTBVA_2,5_2-G-5,08_1x02_P5.08mm_Vertical",1,JVALVE5

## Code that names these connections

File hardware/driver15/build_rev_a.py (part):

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for i,(x,y) in enumerate([(4,4),(236,4),(4,186),(236,186)],1):
    add('H'+str(i),'M3','MountingHole.pretty/MountingHole_3.2mm_M3.kicad_mod',x,y,{})

left=['3V3','ESP_EN','GPIO36','GPIO39','GPIO34','GPIO35','GPIO32','GPIO33','GPIO25','GPIO26','GPIO27','GPIO14',None,'GND','GPIO13',None,None,None,'5V']
right=['GND','GPIO23','GPIO22',None,None,'GPIO21','GND','GPIO19','GPIO18',None,'GPIO17','GPIO16','GPIO4',None,None,None,None,None,None]
for ref,x,labels in [('JESP_L',14,left),('JESP_R',41.5,right)]:
    add(ref,'ESP32_1x19_SPACING_27.5_ASSUMED','Connector_PinSocket_2.54mm.pretty/PinSocket_1x19_P2.54mm_Vertical.kicad_mod',x,14,{str(i+1):v for i,v in enumerate(labels)},notes='Pinout assumed DevKitC V4; spacing and pin order must be checked against actual board.')

# External PCF8575 module via labeled cable, not a guessed module socket.
pcf=['3V3','GND','GPIO16','GPIO17']+[f'PCF_P0{i}' for i in range(6)]
add('JPCF','PCF8575_EXTERNAL_3V3','Connector_PinHeader_2.54mm.pretty/PinHeader_1x10_P2.54mm_Vertical.kicad_mod',60,14,{str(i+1):n for i,n in enumerate(pcf)},notes='Custom cable pin order; not physical PCF module pin order.')
r('RI2C1','4.7k',49,39,'3V3','GPIO16')
r('RI2C2','4.7k',49,43,'3V3','GPIO17')
c('CPCF','100n',65,14,'3V3','GND')

inv={1:(1,2),2:(3,4),3:(5,6),4:(9,8),5:(11,10),6:(13,12)}
pin5={'7':'GND','14':'5V'}
for i,(a,y) in inv.items():pin5[str(a)]=f'PCF_P0{i-1}';pin5[str(y)]=f'VALVE{i}' if i<6 else 'EXP_READY'
add('U5','SN74AHCT04N',DIP14,70,45,pin5)
for i in range(6):r('RPCF'+str(i),'10k',66,47+3*i,'3V3',f'PCF_P0{i}')
c('CU5','100n',82,44,'5V','GND')

signals1=[f'GPIO{i}' for i in [25,18,19,21,22]]+['VALVE1','VALVE2','VALVE3']
signals2=['VALVE4','VALVE5']+[f'GPIO{i}' for i in [26,23,32,33,13]]+['GND']
for u,x,signals in [(1,90,signals1),(2,125,signals2)]:
    pins={'1':'OE_N','19':'OE_N','10':'GND','20':'5V'}
    for i,n in enumerate(signals,1):
        pins[str(i+1)]=n
        if not(u==2 and i==8):pins[str(19-i)]=f'BUF{u}_{i}'
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        if n.startswith('GPIO'):r(f'RIN{u}_{i+1}','47k',x-6,17+3*i,n,'GND')

# Independent missing-pulse shutdown. 123 output Q1 is pin 13, /Q1 is pin 4.
wd={'1':'GND','2':'GPIO4','3':'ESP_EN','8':'GND','9':'GND','10':'GND','11':'GND','13':'WD_OK','14':'WD_CNEG','15':'WD_RC','16':'3V3'}
add('U6','CD74HC123E',DIP16,102,51,wd,notes='Retriggerable missing-pulse detector; RC timeout must be measured at 3V3, not assumed from 5V formula.')
c('CU6','100n',114,50,'3V3','GND')
r('RWD','470k_1pct',115,54,'3V3','WD_RC')
c('CWD','1u_X7R',115,58,'WD_RC','WD_CNEG')
r('RHB','10k',97,50,'GPIO4','GND')
r('RRUN','10k',88,52,'GPIO14','GND')

for i,(control,x) in enumerate([('GPIO14',146),('EXP_READY',161),('WD_OK',176)],1):
    collector='OE_N' if i==1 else f'EN_CHAIN{i-1}'
    emitter='GND' if i==3 else f'EN_CHAIN{i}'
    add(f'QEN{i}','2N3904','Package_TO_SOT_THT.pretty/TO-92_Inline_Wide.kicad_mod',x,52,{'1':emitter,'2':f'EN_B{i}','3':collector})
    r(f'RENB{i}','10k',x+1,46,control,f'EN_B{i}')
    r(f'RENP{i}','100k',x+1,59,f'EN_B{i}','GND')
r('ROE','10k',144,40,'5V','OE_N')
add('JSTOP','INTERLOCK_NC_REQUIRED','Connector_PinHeader_2.54mm.pretty/PinHeader_1x02_P2.54mm_Vertical.kicad_mod',187,48,{'1':'WD_OK','2':'WD_LINK'})
# Route watchdog base resistor via physical NC interlock. Opening interlock disables load.
for pad in fps['RENB3'].Pads():
    if pad.GetNumber()=='1':pad.SetNet(net('WD_LINK'))
next(cmp for cmp in components if cmp['ref']=='RENB3')['pins']['1']='WD_LINK'

# External regulated 5 V module connected with separate IN/OUT terminals.
add('J12','12V_INPUT_EXTERNAL_FUSE_5A_REQUIRED',TERM,215,13,{'1':'12V_LOAD','2':'GND'},notes='External DC fuse mandatory upstream; polarity must be verified; no integrated reverse polarity protection.')
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
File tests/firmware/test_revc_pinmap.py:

"""Đối chiếu pad/net PCB Rev C với chân firmware, không cần KiCad hay tải thật."""
import re
import unittest
from pathlib import Path

ROOT = Path(__file__).resolve().parents[2]
PCB_PATH = ROOT / 'AI gen/KiCad/RevC/scentstation-rev-c.kicad_pcb'


def parse_sexpr(source):
    stack, roots = [], []
    for token in re.findall(r'"(?:\\.|[^"\\])*"|[^\s()]+|[()]', source):
        if token == '(':
            node = []
            (stack[-1] if stack else roots).append(node)
            stack.append(node)
        elif token == ')':
            stack.pop()
        else:
            stack[-1].append(token.strip('"'))
    return roots[0]


def children(node, kind):
    return [item for item in node if isinstance(item, list) and item and item[0] == kind]


@unittest.skipUnless(PCB_PATH.is_file(), 'Local PCB in AI gen is not included in the repository')
class RevCPinmap(unittest.TestCase):
    @classmethod
    def setUpClass(cls):
        pcb = parse_sexpr(PCB_PATH.read_text(encoding='utf-8'))
        cls.pads = {}
        for footprint in children(pcb, 'footprint'):
            ref = next(p[2] for p in children(footprint, 'property') if p[1] == 'Reference')
            cls.pads[ref] = {p[1]: children(p, 'net')[0][2] for p in children(footprint, 'pad') if children(p, 'net')}
        cls.firmware = (ROOT / 'arduino/ScentStationValveDevice/ScentStationValveDevice.ino').read_text(encoding='utf-8')
        cls.config = (ROOT / 'arduino/ScentStationValveDevice/config.example.h').read_text(encoding='utf-8')

    def test_pumps_lights_buttons(self):
        for name, gpios, ref, pins in [
            ('PUMP', [25, 18, 19, 21, 22], 'U1', ['2', '3', '4', '5', '6']),
            ('LIGHT', [26, 23, 32, 33, 13], 'U2', ['4', '5', '6', '7', '8']),
        ]:
            actual = re.search(name + r'_PINS\[SLOT_COUNT\] = \{([^}]+)\}', self.firmware)
            self.assertIsNotNone(actual)
            self.assertEqual([int(x) for x in actual[1].split(',')], gpios)
            self.assertEqual([self.pads[ref][pin] for pin in pins], [f'GPIO{x}' for x in gpios])
        gpios = [27, 34, 35, 36, 39]
        actual = re.search(r'BUTTON_PINS\[SLOT_COUNT\] = \{([^}]+)\}', self.firmware)
        self.assertEqual([int(x) for x in actual[1].split(',')], gpios)
        for i, gpio in enumerate(gpios, 1):
            self.assertEqual(self.pads[f'JBTN{i}'], {'1': 'GND', '2': f'GPIO{gpio}'})

    def test_expander_gate_watchdog(self):
        self.assertEqual(self.pads['JPCF1'], dict(zip(map(str, range(1, 11)), ['3V3', 'GND', 'GPIO16', 'GPIO17'] + [f'PCF_P0{i}' for i in range(6)])))
        for macro, value in [('VALVE_I2C_SDA', 16), ('VALVE_I2C_SCL', 17), ('LOAD_RUN_REQUEST_PIN', 14), ('DRIVER_WATCHDOG_PIN', 4)]:
            self.assertRegex(self.config, rf'#define {macro}\s+{value}\b')
            self.assertRegex(self.firmware, rf'#define {macro}\s+{value}\b')
        self.assertEqual(self.pads['U6']['2'], 'GPIO4')
        for pin, net in [('1', 'PCF_P00'), ('2', 'VALVE1'), ('3', 'PCF_P01'), ('4', 'VALVE2'), ('5', 'PCF_P02'), ('6', 'VALVE3'), ('9', 'PCF_P03'), ('8', 'VALVE4'), ('11', 'PCF_P04'), ('10', 'VALVE5'), ('13', 'PCF_P05'), ('12', 'EXP_READY')]:
            self.assertEqual(self.pads['U5'][pin], net)

    def test_revc_power_changes(self):
        self.assertEqual(self.pads['J12'], {'1': '12V_IN', '2': 'GND'})
        self.assertEqual(self.pads['F1'], {'1': '12V_IN', '2': '12V_LOAD'})
        for i in range(11, 16):
            self.assertEqual(self.pads[f'D{i}'], {'1': '12V_LOAD', '2': f'DRAIN{i}'})
        self.assertEqual(self.pads['JSTOP1'], {'1': 'WD_OK', '2': 'WD_LINK'})


if __name__ == '__main__':
    unittest.main()
